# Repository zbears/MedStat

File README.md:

# MedStat
A wearable medical wristband

## Eagle Setup
In order to modify the cirucits in Eagle, clone the git repo then open Eagle. Go to Options->Directories and add the /circuits/libraries folder to your libraries path. Then add the /circuits folder to your projects path.

## Creating/Modifying Circuits
To create or modify a circuit, please create a separate branch from master. Go into the /circuits folder and create a directory whose name corresponds to the circuit you are creating. When you've finished creating the circuit, submit a pull request and have your circuit verified by one engineer. Once the circuit is verified, make the modifications to the main MedStat eagle project to include your circuit, submit another pull request to master, have one other engineer verify your circuit, then merge your branch with master. Do not delete your branch after merging with master.

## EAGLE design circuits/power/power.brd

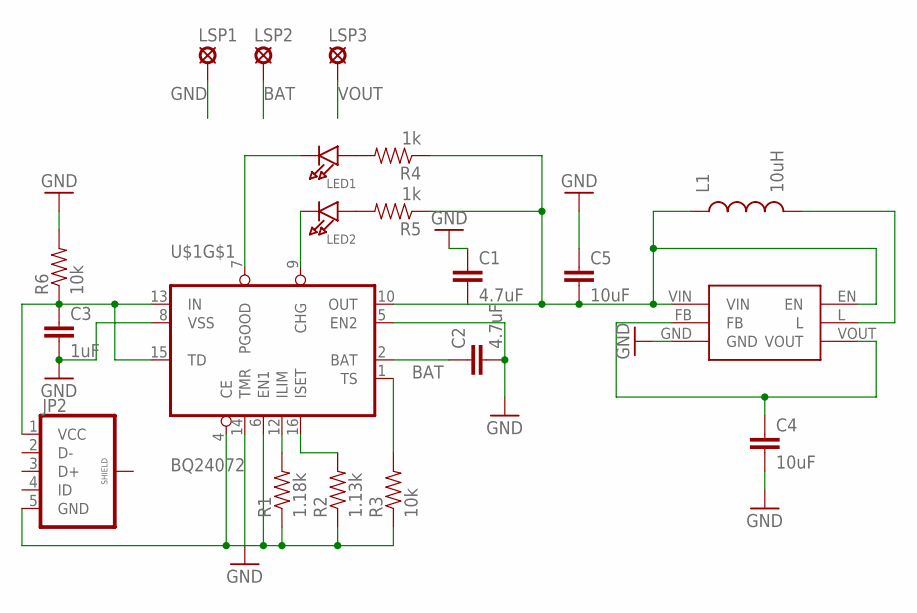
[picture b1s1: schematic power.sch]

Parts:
C1, C2: 4.7uF; 0603-CAP
C3: 1uF; 0603-CAP
C4, C5: 10uF; 0603-CAP
JP2: USB_MICROB_PLUG-SMT; MICRO-B-SMT
L1: 10uH; 0603
LED1, LED2: LED0603; CHIPLED_0603
LSP1, LSP2, LSP3: LSP10
R1: 1.18k; 0603-RES
R2: 1.13k; 0603-RES
R3, R6: 10k; 0603-RES
R4, R5: 1k; 0603-RES
U$1: BQ24072; S-PVQFN-N16
U$3: TLV61225; SC70

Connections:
BAT: C2.1, LSP2.MP, U$1.2 (BAT)
GND: C1.1, C2.2, C3.2, C4.2, C5.1, JP2.5 (GND), LSP1.MP, R1.1, R2.1, R3.1, R6.2, U$1.4 (CE), U$1.5 (EN2), U$1.6 (EN1), U$1.8 (VSS), U$1.14 (TMR)
unnamed: L1.2, U$3.L
unnamed: R1.2, U$1.12 (ILIM)
unnamed: R2.2, U$1.16 (ISET)
unnamed: R3.2, U$1.1 (TS)
unnamed: C1.2, C5.2, L1.1, R4.1, R5.1, U$1.10 (OUT), U$3.EN, U$3.VIN
unnamed: LED1.A, R4.2
unnamed: LED2.A, R5.2
unnamed: LED2.C, U$1.9 (CHG)
unnamed: LED1.C, U$1.7 (PGOOD)
unnamed: C3.1, JP2.1 (VCC), R6.1, U$1.13 (IN), U$1.15 (TD)
VOUT: C4.1, LSP3.MP, U$3.FB, U$3.VOUT

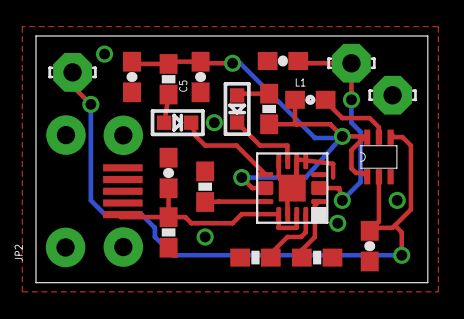
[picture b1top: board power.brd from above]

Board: 2 copper layers, 21.8 x 13.7 mm, 20 parts (0 on the bottom side), 13 nets.

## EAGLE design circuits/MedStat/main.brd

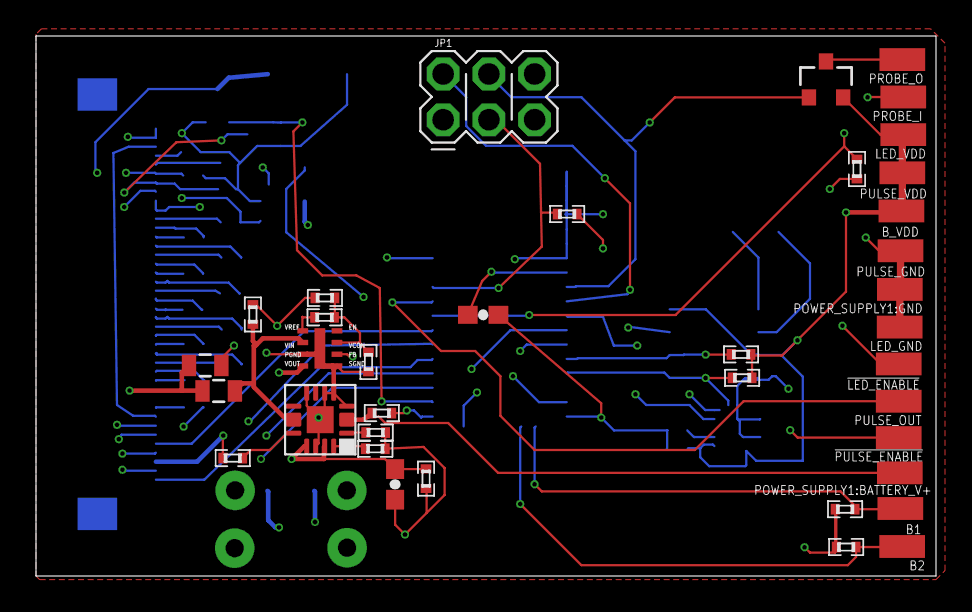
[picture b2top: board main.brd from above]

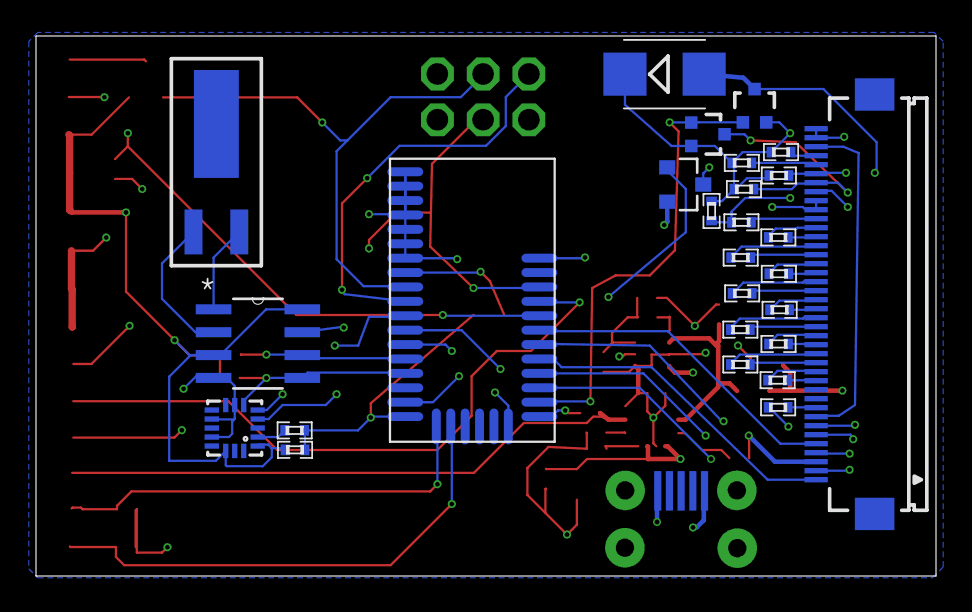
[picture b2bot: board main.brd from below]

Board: 4 copper layers, 50.0 x 30.0 mm, 65 parts (28 on the bottom side), 60 nets.

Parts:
!LED_ENABLE: SMD1,27-2,54
!PULSE_ENABLE: SMD1,27-2,54
B1, B2: SMD1,27-2,54
B_VDD: SMD1,27-2,54
C1: 1uF; 0603-CAP
C2: 0.1uF; 0402
C3: 4.7uF; 0402
EPAPER_DRIVER1:C1, EPAPER_DRIVER1:C2, EPAPER_DRIVER1:C3, EPAPER_DRIVER1:C4, EPAPER_DRIVER1:C5, EPAPER_DRIVER1:C6, EPAPER_DRIVER1:C7, EPAPER_DRIVER1:C8, EPAPER_DRIVER1:C9, EPAPER_DRIVER1:C10, EPAPER_DRIVER1:C12, EPAPER_DRIVER1:C13, EPAPER_DRIVER1:C14, EPAPER_DRIVER1:C15: 2.2uF; 0402
EPAPER_DRIVER1:C11: 1uF; 0402
EPAPER_DRIVER1:D2: B24013F; SMB
EPAPER_DRIVER1:Q1, EPAPER_DRIVER1:Q2: MOSFET-NCHANNEL2N7002PW; SOT323
EPAPER_DRIVER1:R1: 2k; 0402
EPAPER_DRIVER1:U$1: P-CHANNEL-MOSFET; SOT23-3
EPAPER_DRIVER1:X1: FH12-40S-0.5SH
JP1: 2X3_POGO
LED_GND: SMD1,27-2,54
LED_VDD: SMD1,27-2,54
POWER_SUPPLY1:BATTERY_V+, POWER_SUPPLY1:GND: SMD1,27-2,54
POWER_SUPPLY1:C1, POWER_SUPPLY1:C4: 4.7uF; 0402
POWER_SUPPLY1:C2, POWER_SUPPLY1:C3: 10uF; 0805
POWER_SUPPLY1:C6: 470pF; 0402
POWER_SUPPLY1:C7: 1uF; 0603-CAP
POWER_SUPPLY1:JP1: MICRO-B-SMT
POWER_SUPPLY1:R1: 1.18k; 0402
POWER_SUPPLY1:R2: 1.13k; 0402
POWER_SUPPLY1:R3, POWER_SUPPLY1:R4: 10k; 0402
POWER_SUPPLY1:R5: 150k; 0402
POWER_SUPPLY1:R6: 118k; 0402
POWER_SUPPLY1:U$1: BQ24072; S-PVQFN-N16
POWER_SUPPLY1:U$2: LMZ10500
PROBE_I: SMD1,27-2,54
PROBE_O: SMD1,27-2,54
PULSE_GND: SMD1,27-2,54
PULSE_OUT: SMD1,27-2,54
PULSE_VDD: SMD1,27-2,54
R1, R5, R6: 10k; 0402
R2, R3: 4.7k; 0402
R4: 1M; 0402
U1: BLE113-A
U2: MMA8452Q; QFN-16_0.5MM
U3: BQ32000DR; SOIC127P600X175-8N
U$1: P-CHANNEL-MOSFET; SOT23-3
Y1: CRYSTAL_CYL_2X6MM_SMT

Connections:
3.3V: B_VDD.1, C1.2, C3.1, EPAPER_DRIVER1:U$1.2, JP1.P$1, LED_VDD.1, POWER_SUPPLY1:C2.1, POWER_SUPPLY1:U$2.FB, POWER_SUPPLY1:U$2.VOUT, PULSE_VDD.1, R1.2, R2.2, R3.2, U1.AVDD, U1.DVDD, U2.1, U2.14, U3.3, U3.8, U$1.2
!RESET: JP1.P$3, R1.1, U1.RESET
EPAPER_DRIVER1:BORDER: EPAPER_DRIVER1:X1.8, EPAPER_DRIVER1:X1.38
EPAPER_DRIVER1:C11M: EPAPER_DRIVER1:C10.2, EPAPER_DRIVER1:X1.28
EPAPER_DRIVER1:C11P: EPAPER_DRIVER1:C10.1, EPAPER_DRIVER1:X1.29
EPAPER_DRIVER1:C12M: EPAPER_DRIVER1:C9.2, EPAPER_DRIVER1:X1.26
EPAPER_DRIVER1:C12P: EPAPER_DRIVER1:C9.1, EPAPER_DRIVER1:X1.27
EPAPER_DRIVER1:C13M: EPAPER_DRIVER1:C8.2, EPAPER_DRIVER1:X1.24
EPAPER_DRIVER1:C13P: EPAPER_DRIVER1:C8.1, EPAPER_DRIVER1:X1.25
EPAPER_DRIVER1:C14M: EPAPER_DRIVER1:C7.2, EPAPER_DRIVER1:X1.22
EPAPER_DRIVER1:C14P: EPAPER_DRIVER1:C7.1, EPAPER_DRIVER1:X1.23
EPAPER_DRIVER1:C15M: EPAPER_DRIVER1:C6.2, EPAPER_DRIVER1:X1.20
EPAPER_DRIVER1:C15P: EPAPER_DRIVER1:C6.1, EPAPER_DRIVER1:X1.21
EPAPER_DRIVER1:C16M: EPAPER_DRIVER1:C5.2, EPAPER_DRIVER1:X1.18
EPAPER_DRIVER1:C16P: EPAPER_DRIVER1:C5.1, EPAPER_DRIVER1:X1.19
EPAPER_DRIVER1:C21M: EPAPER_DRIVER1:C4.2, EPAPER_DRIVER1:X1.16
EPAPER_DRIVER1:C21P: EPAPER_DRIVER1:C4.1, EPAPER_DRIVER1:X1.17
EPAPER_DRIVER1:C31M: EPAPER_DRIVER1:C3.2, EPAPER_DRIVER1:X1.14
EPAPER_DRIVER1:C31P: EPAPER_DRIVER1:C3.1, EPAPER_DRIVER1:X1.15
EPAPER_DRIVER1:C32M: EPAPER_DRIVER1:C2.2, EPAPER_DRIVER1:X1.12
EPAPER_DRIVER1:C32P: EPAPER_DRIVER1:C2.1, EPAPER_DRIVER1:X1.13
EPAPER_DRIVER1:E_VDD: EPAPER_DRIVER1:U$1.3, EPAPER_DRIVER1:X1.31, EPAPER_DRIVER1:X1.32
EPAPER_DRIVER1:VCL: EPAPER_DRIVER1:C1.2, EPAPER_DRIVER1:X1.9
EPAPER_DRIVER1:VCOM_DRIVER: EPAPER_DRIVER1:R1.2, EPAPER_DRIVER1:X1.30
EPAPER_DRIVER1:VDH: EPAPER_DRIVER1:C14.2, EPAPER_DRIVER1:X1.36
EPAPER_DRIVER1:VDL: EPAPER_DRIVER1:C15.2, EPAPER_DRIVER1:X1.37
EPAPER_DRIVER1:VGH: EPAPER_DRIVER1:C12.2, EPAPER_DRIVER1:Q2.3, EPAPER_DRIVER1:X1.34
EPAPER_DRIVER1:VGL: EPAPER_DRIVER1:C13.2, EPAPER_DRIVER1:D2.A, EPAPER_DRIVER1:Q1.3, EPAPER_DRIVER1:X1.35
EPAPER_DRIVER1:VST: EPAPER_DRIVER1:C11.2, EPAPER_DRIVER1:R1.1, EPAPER_DRIVER1:X1.39, EPAPER_DRIVER1:X1.40
GND: C1.1, C2.1, C3.2, EPAPER_DRIVER1:C1.1, EPAPER_DRIVER1:C11.1, EPAPER_DRIVER1:C12.1, EPAPER_DRIVER1:C13.1, EPAPER_DRIVER1:C14.1, EPAPER_DRIVER1:C15.1, EPAPER_DRIVER1:D2.C, EPAPER_DRIVER1:Q1.2, EPAPER_DRIVER1:Q2.2, EPAPER_DRIVER1:X1.3, EPAPER_DRIVER1:X1.33, JP1.P$5, LED_GND.1, POWER_SUPPLY1:C1.1, POWER_SUPPLY1:C2.2, POWER_SUPPLY1:C3.2, POWER_SUPPLY1:C4.1, POWER_SUPPLY1:C6.1, POWER_SUPPLY1:C7.2, POWER_SUPPLY1:GND.1, POWER_SUPPLY1:JP1.5, POWER_SUPPLY1:R1.1, POWER_SUPPLY1:R2.1, POWER_SUPPLY1:R3.1, POWER_SUPPLY1:R4.1, POWER_SUPPLY1:R5.1, POWER_SUPPLY1:U$1.4, POWER_SUPPLY1:U$1.5, POWER_SUPPLY1:U$1.6, POWER_SUPPLY1:U$1.8, POWER_SUPPLY1:U$1.14, POWER_SUPPLY1:U$2.PGND, POWER_SUPPLY1:U$2.SGND, PULSE_GND.1, R4.2, R5.1, R6.1, U1.GND, U1.GND@2, U1.GND@3, U1.GND@4, U1.GND@5, U1.GND@6, U1.GND@7, U1.GND@8, U1.GND@9, U1.GND@10, U2.5, U2.7, U2.10, U2.12, U3.4
unnamed: U3.2, Y1.2
unnamed: C2.2, U2.2
unnamed: PROBE_O.1, U$1.3
OSCI: U3.1, Y1.1
P0_0: PULSE_OUT.1, U1.P0_0
P0_1: PROBE_I.1, R4.1, U1.P0_1
P0_2: EPAPER_DRIVER1:X1.5, U1.P0_2
P0_3: EPAPER_DRIVER1:X1.6, U1.P0_3
P0_4: EPAPER_DRIVER1:X1.1, U1.P0_4
P0_5: EPAPER_DRIVER1:X1.4, U1.P0_5
P0_6: EPAPER_DRIVER1:X1.2, U1.P0_6
P0_7: EPAPER_DRIVER1:Q1.1, EPAPER_DRIVER1:Q2.1, U1.P0_7
P1_0: U1.P1_0, U3.7
P1_4: B2.1, R6.2, U1.P1_4
P1_5: B1.1, R5.2, U1.P1_5
P1_6: EPAPER_DRIVER1:U$1.1, U1.P1_6
P1_7: EPAPER_DRIVER1:X1.7, U1.P1_7
P2_0: !PULSE_ENABLE.1, U1.P2_0
P2_1: !LED_ENABLE.1, JP1.P$2, U1.P2_1
P2_2: JP1.P$4, U1.P2_2, U$1.1
POWER_SUPPLY1:BATTERY_V+: POWER_SUPPLY1:BATTERY_V+.1, POWER_SUPPLY1:C1.2, POWER_SUPPLY1:U$1.2
POWER_SUPPLY1:CHG_OUT: POWER_SUPPLY1:C3.1, POWER_SUPPLY1:C4.2, POWER_SUPPLY1:U$1.10, POWER_SUPPLY1:U$2.VIN
POWER_SUPPLY1:N$1: POWER_SUPPLY1:C6.2, POWER_SUPPLY1:R5.2, POWER_SUPPLY1:R6.1, POWER_SUPPLY1:U$2.VCON
POWER_SUPPLY1:N$2: POWER_SUPPLY1:R6.2, POWER_SUPPLY1:U$2.VREF
POWER_SUPPLY1:N$3: POWER_SUPPLY1:R2.2, POWER_SUPPLY1:U$1.16
POWER_SUPPLY1:N$5: POWER_SUPPLY1:R1.2, POWER_SUPPLY1:U$1.12
POWER_SUPPLY1:N$7: POWER_SUPPLY1:R3.2, POWER_SUPPLY1:U$1.1
POWER_SUPPLY1:VCC: POWER_SUPPLY1:C7.1, POWER_SUPPLY1:JP1.1, POWER_SUPPLY1:R4.2, POWER_SUPPLY1:U$1.13, POWER_SUPPLY1:U$1.15
SCL: R2.1, U1.SCL, U2.4, U3.6
SDA: R3.1, U1.SDA, U2.6, U3.5

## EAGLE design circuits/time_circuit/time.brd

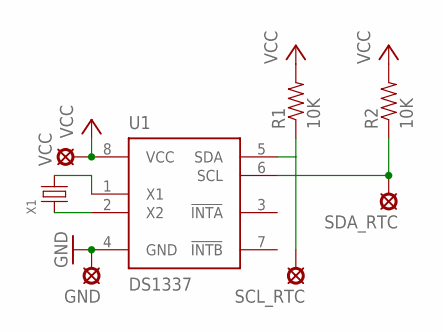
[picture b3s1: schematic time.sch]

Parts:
GND: SE13
R1, R2: 10K; 0603-RES
SCL_RTC: SE13
SDA_RTC: SE13
U1: DS1337; UMAX8
VCC: SE13
X1: CRYSTAL8X3.5MM; CRYSTAL-8X3.5MM

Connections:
GND: GND.MP, U1.4 (GND)
unnamed: U1.2 (X2), X1.1
unnamed: U1.1 (X1), X1.4 (3)
unnamed: R1.1, SCL_RTC.MP, U1.5 (SDA)
unnamed: R2.1, SDA_RTC.MP, U1.6 (SCL)
VCC: R1.2, R2.2, U1.8 (VCC), VCC.MP

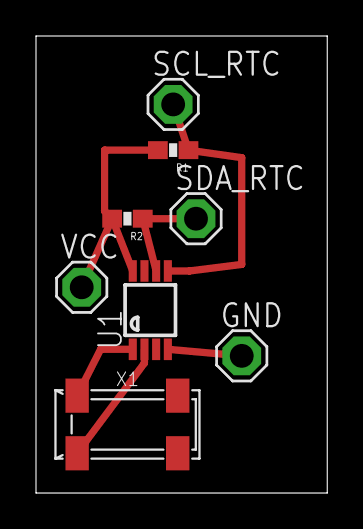
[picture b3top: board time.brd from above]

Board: 2 copper layers, 16.2 x 25.4 mm, 8 parts (0 on the bottom side), 6 nets.

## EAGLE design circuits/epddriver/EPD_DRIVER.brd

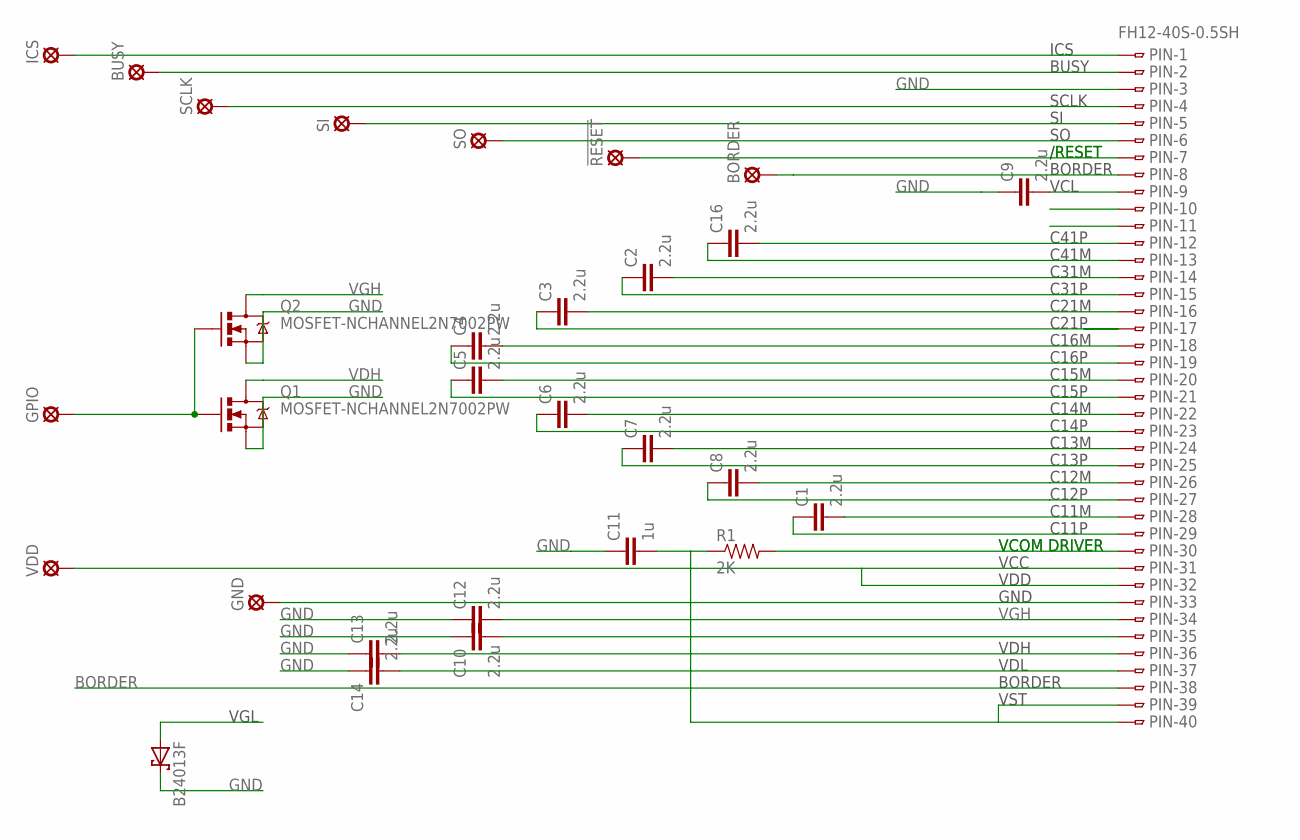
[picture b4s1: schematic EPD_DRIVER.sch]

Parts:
!RESET: SE11
B24013F: SCHOTTKY-DIODESMD; SMB
BORDER: SE11
BUSY: SE11
C1, C2, C3, C4, C5, C6, C7, C8, C9, C10, C12, C13, C14, C16: 2.2u; 0603-CAP
C11: 1u; 0603-CAP
GND: SE11
GPIO: SE11
ICS: SE11
PIN: FH12-40S-0.5SH
Q1, Q2: MOSFET-NCHANNEL2N7002PW; SOT323
R1: 2K; 0603-RES
SCLK: SE11
SI: SE11
SO: SE11
VDD: SE11

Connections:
BORDER: BORDER.MP, PIN.8, PIN.38
GND: B24013F.C, C9.1, C10.1, C11.1, C12.1, C13.1, C14.1, PIN.3, Q1.2 (S), Q2.2 (S)
ICS: ICS.MP, PIN.1
unnamed: PIN.4, SCLK.MP
unnamed: BUSY.MP, PIN.2
unnamed: PIN.5, SI.MP
unnamed: PIN.6, SO.MP
unnamed: !RESET.MP, PIN.7
unnamed: GND.MP, PIN.33
unnamed: C16.2, PIN.12
unnamed: C16.1, PIN.13
unnamed: C2.2, PIN.14
unnamed: C2.1, PIN.15
unnamed: C3.2, PIN.16
unnamed: C3.1, PIN.17
unnamed: C4.2, PIN.18
unnamed: C4.1, PIN.19
unnamed: C5.2, PIN.20
unnamed: C5.1, PIN.21
unnamed: C6.2, PIN.22
unnamed: C6.1, PIN.23
unnamed: C7.2, PIN.24
unnamed: C7.1, PIN.25
unnamed: C8.2, PIN.26
unnamed: C8.1, PIN.27
unnamed: C1.2, PIN.28
unnamed: C1.1, PIN.29
unnamed: PIN.30, R1.2
unnamed: PIN.31, PIN.32, VDD.MP
unnamed: GPIO.MP, Q1.1 (G), Q2.1 (G)
VCL: C9.2, PIN.9
VDH: C13.2, PIN.36, Q1.3 (D)
VDL: C14.2, PIN.37
VGH: C10.2, PIN.34, Q2.3 (D)
VGL: B24013F.A, C12.2, PIN.35
VST: C11.2, PIN.39, PIN.40, R1.1

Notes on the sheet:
ICS
BUSY
SCLK
/RESET
BORDER
VCL
C41P
C41M
C31M
C31P
C21M
C21P
C16M
C16P
C15M
C15P
C14M
C14P
C13M
C13P
C12M
C12P
C11M
C11P
VCOM DRIVER
VCC
VDD
GND
VDH
VDL
VST
VGL

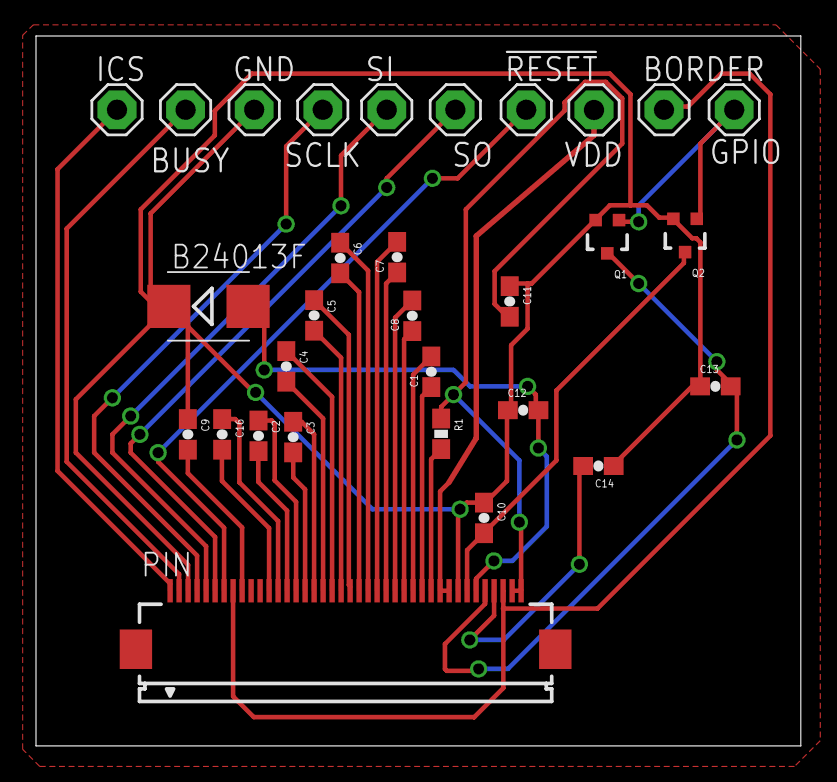
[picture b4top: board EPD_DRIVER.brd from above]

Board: 2 copper layers, 42.5 x 39.4 mm, 30 parts (0 on the bottom side), 36 nets.

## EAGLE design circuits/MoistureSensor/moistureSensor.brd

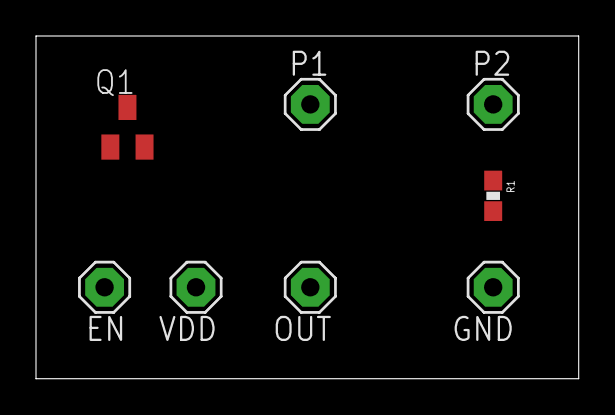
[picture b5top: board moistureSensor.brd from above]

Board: 2 copper layers, 30.1 x 19.0 mm, 8 parts (0 on the bottom side), 5 nets, no tracks yet.

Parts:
EN: MCS10B
GND: MCS10B
OUT: MCS10B
P1, P2: MCS10B
Q1: BSS84; SOT23
R1: 1M; 0603-RES
VDD: MCS10B

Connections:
GND: GND.MP, R1.2
unnamed: P2.MP, R1.1
unnamed: EN.MP, Q1.1
unnamed: OUT.MP, P1.MP, Q1.3
VDD: Q1.2, VDD.MP

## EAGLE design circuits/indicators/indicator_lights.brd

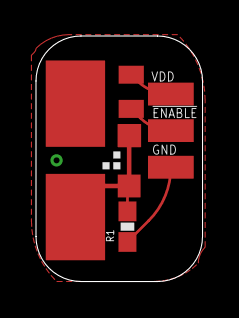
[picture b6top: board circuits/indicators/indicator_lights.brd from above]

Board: 2 copper layers, 9.3 x 13.6 mm, 6 parts (0 on the bottom side), 5 nets.

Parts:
!ENABLE: SMD1,27-2,54
GND: SMD1,27-2,54
LED1: LS E67B; P-LCC-4-3
Q1: BSS84; SOT23
R1: 36; 0603-RES
VDD: SMD1,27-2,54

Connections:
!ENABLE: !ENABLE.1, Q1.1
GND: GND.1, R1.1
unnamed: LED1.2, Q1.3
unnamed: LED1.1, LED1.3, LED1.4, R1.2
VDD: Q1.2, VDD.1

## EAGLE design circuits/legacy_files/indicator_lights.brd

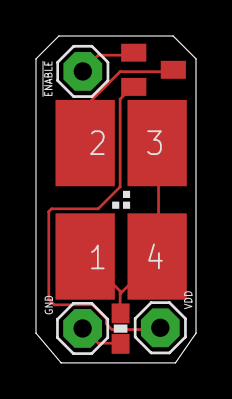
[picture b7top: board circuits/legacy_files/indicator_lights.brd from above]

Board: 2 copper layers, 8.9 x 18.2 mm, 6 parts (0 on the bottom side), 5 nets.

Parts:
LED1: LS E67B; P-LCC-4-3
LSP1, LSP2, LSP3: MCS10B
Q1: BSS84; SOT23
R1: 36; 0603-RES

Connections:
!ENABLE: LSP1.MP, Q1.1
GND: LSP3.MP, R1.1
unnamed: LED1.2, Q1.3
unnamed: LED1.1, LED1.3, LED1.4, R1.2
VDD: LSP2.MP, Q1.2

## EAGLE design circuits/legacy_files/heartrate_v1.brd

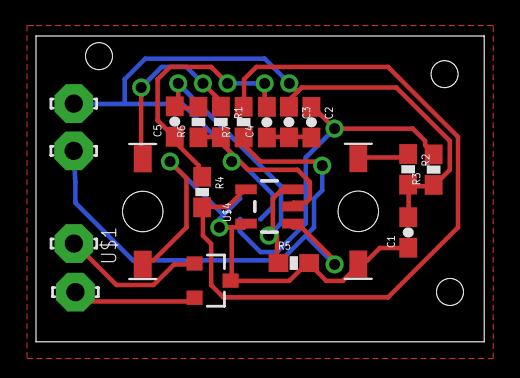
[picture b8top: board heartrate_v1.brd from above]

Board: 2 copper layers, 24.9 x 17.0 mm, 21 parts (1 on the bottom side), 12 nets.

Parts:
!ENABLE: LSP10
C1: 2.2uF; 0603-CAP
C2, C3, C4: 4.7 uF; 0603-CAP
C5: 2.2 uF; 0603-CAP
GND: LSP10
OUT: LSP10
R1, R2: 715; 0603-RES
R3: 12k; 0603-RES
R4: 10k; 0603-RES
R5, R6: 100k; 0603-RES
R7: 3.3M; 0603-RES
U$1, U$2: DSAH3717
U$3: APDS-9008
U$4: MCP6001; SOT23-5
U$5: P-CHANNEL-MOSFET; SOT23-3
VDD: LSP10

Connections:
GND-ISO: C1.2, C3.1, GND.MP, R1.2, R2.2, R3.1, R6.1, U$3.GND, U$4.VSS
unnamed: R1.1, U$1.G
unnamed: U$5.2, VDD.MP
unnamed: !ENABLE.MP, U$5.1
unnamed: R2.1, U$2.G
unnamed: C2.1, R3.2, U$3.OUT
unnamed: C2.2, C3.2, C4.1
unnamed: C4.2, C5.1, R4.1
unnamed: C5.2, R5.1, R6.2, U$4.VIN+
unnamed: R4.2, R7.2, U$4.VIN-
OUT: OUT.MP, R7.1, U$4.VOUT
VDD: C1.1, R5.2, U$1.V, U$2.V, U$3.VCC, U$4.VDD, U$5.3

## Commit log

2015-09-20 Added libraries
2015-09-20 Create README.md
    Added guidelines for creating+modifying circuits
2015-09-20 Added custom through-hole LED schematic
2015-09-21 Added pulse sensing circuitry
2015-09-21 Added accelerometer circuit
2015-09-22 began adding power circuit to main schematic. have not added in voltage regulator yet
2015-09-22 added voltage regulator. ready for first round bear check
2015-09-22 Central class with scanning and connecting functions to peripherals
2015-09-22 Central class with skeleton for scanning and connecting to peripherals
2015-09-23 Created indicator schematic+board
2015-09-23 added junctions
2015-09-23 Added a driver circuit meant to interface with the 1.44' EPD.
2015-09-25 changed small things around
2015-10-04 Integrated LED pins with main schematic
2015-10-04 Created pulse sensor layout
2015-10-04 Tied in moisture sensor pins
2015-10-04 Added pulse sensor ports
2015-10-06 switched back to old branch
2015-10-06 remade power circuit. still need to add in voltage regulator
2015-10-07 added in linear regulator to power circuit
2015-10-08 Merged the EPD driver circuit into the main schematic.
2015-10-08 Peripheral device entry class
2015-10-08 Peripheral devices entry class
2015-10-08 Moisture sensor schematic
2015-10-09 Added Moisture Sensor layout
2015-10-09 Moisture sesnsor layout final
2015-10-10 created new power circuit in different branch and folder
2015-10-10 made custom file and added buck converter into circuit
2015-10-10 moved location of new custom Library: LMZ10500
2015-10-12 Integrated EPD driver to main schematic.
2015-10-14 Added Blink Sketch
    Added a sketch that makes the BLE113 blink an LED on pin P0_0 on a 1s
    interval
2015-10-16 Integrated EPD into main schematic.
2015-10-17 Time circuit schematic with ds1307
2015-10-18 fixed the footprint of the buck converter
2015-10-19 Swapped probe and resistor positions
2015-10-20 Fixed EPD_DRIVER schematic and created layout for it
2015-10-20 Moisture sensor schematic and layout
2015-10-20 Made sure wires have same name
2015-10-21 Integrated wires to main schematic
2015-10-21 Time circuit layout drc
2015-10-21 Update oscillator with SMT part
2015-10-21 Update layout
2015-10-21 time circuit revised
2015-10-21 added power circuit to main schematic
2015-10-21 time circuit integration revised
2015-10-21 Replaced ds1307 with ds1337
2015-10-22 Copying time circuit into new branch
2015-10-22 Integrate into main schematic
2015-10-23 finished layout of power circuit
2015-10-23 added pull up resistor to reset button
2015-10-25 branch create
2015-10-25 Added in revised power circuit layout
2015-10-25 changed resistor and capacitor sizes
2015-10-26 Completed master schematic
2015-10-26 Finished final board layout round 1
2015-10-26 finished new heart rate sensor layout
2015-10-27 remade heart rate sensor
2015-10-28 nothing
2015-10-28 deleted dimension lines from heart sensor layout
2015-10-29 Setting up main android app project
2015-11-02 Added LED blinking VIA BLE control
    A LED attached to P0_0 now illuminates when a connection is made with
    the module and a LED on pin P0_1 can be toggled on and off by sending a
    1 or a 0 byte to the LED toggle service.
2015-11-02 Cleaned up code + Added accelerometer
    Removed some currently unneeded features so @Millerj1994 will have to
    add back in pulse timers when merging. I can help you with this.
2015-11-02 Added new LED layout
2015-11-10 changed LMZ10500 library. updated power schematic and switched out usb. Made new power layout.
2015-11-10 made power board ready for order. Want to check with zach
2015-11-12 moved power circuit to legacy files
2015-11-13 Android full app
2015-11-13 stuff I dont know
2015-11-17 made new main board. Horrry SHIT
2015-11-18 made copies of the main board schematic and layout
2015-12-10 Final Code and Rough 3D

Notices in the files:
parts and their libraries:
SparkFun-Passives: Licensing: Creative Commons ShareAlike 4.0 International - https://creativecommons.org/licenses/by-sa/4.0
microbuilder: This work is placed in the public domain, and may be freely used for commercial and non-commercial work with the following conditions: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
